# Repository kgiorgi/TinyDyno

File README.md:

# TinyDyno

An ESP32-S3 board that measures the speed and energy efficiency of one neural network inference.

**What is it exactly?**
TinyDyno is a custom 72 by 72 mm, 2 layered PCB based on ESP32-S3.It is basically a test bench for machine learning on tiny devices (AKA edgeAI). It runs a neural network based on the data from sensors and measures every inference for time and energy. Time is how long the inference took and energy is how much ESP32-S3 has used during it.

To account for actual use cases it has an IMU(motion sensor) and a microphone which are for gesture recognition and keyword detector so the usual run look something like this:
1. Record the input from either sensors
2. Run the same model on the same input but with different libraries.(My kernels VS Espressif's ESP-DL VS TensorFlow Lite Micro)
3. Measure each run using the INA226 (power monitor) which reports current/voltage going into the ESP32-S3 which does the power over time math
4. Get the results and make conclusions

(A test pad (TP1) goes high during each inference, so the timing can be checked independently with an oscilloscope or logic analyzer.)

**The WHY behind it all**

Wanting to optimize the field I am currently curious about (AI) I brainstormed for a bit and came to the conclusion that you can't optimize something that you can't measure. After a bit of digging I found few issues it would solve on top of the qol it would provide for me:
1. Most benchmarks only report speed so a faster kernel that uses more power can still drain the battery sooner.
2. The USB power meters are quite slow. They update a few times per second, while one inference takes about 5–50 ms.

(Also it's not like you can find stuff like this easily to buy)

**how does it work?**

**Power: two separate 3.3V rails**

USB-C gives 5V and two separate 3.3V regulators split it into two rails:
1. **Measured rail (3V3_MEAS):** 5V goes through regulator U2, then solder jumper JP1, then the 75 mOhm shunt resistor R3 and then into the ESP32-S3. The ESP32 is the only thing on this rail.
2. **Peripheral rail (3V3_PERIPH):** 5V goes through regulator U1 to everything else (INA226, IMU, mic, LED, pull-ups).

So none of the sensor or LED current goes through the shunt and the measurement is only the ESP32.

**Measuring power**

Current going through the shunt makes a small voltage across it (V = I * R). For example at 100mA it's 0.1A * 0.075 Ohm = 7.5mV, which is tiny, so the INA226 (U3) does the job:
1. measures the voltage across the shunt to get the current
2. measures the 3.3V rail to get the voltage
3. multiplies them to get power
4. pulls its ALERT pin low when a new reading is ready so the ESP32 knows when to read it

The shunt is read through a separate pair of thin traces that go straight from the shunt's pads to the INA226 (Kelvin sensing), so the voltage drop on the thick power traces doesn't mess up the reading.

**From power to energy and time**

Energy = power * time, so during an inference the ESP32 reads the power about once a millisecond and keeps adding up power * time. Time comes from the ESP32's internal microsecond timer.

One measurement looks like this:
1. Load the recorded input
2. Set TP1 high, start the timer and the energy sum
3. Run the model
4. Set TP1 low, stop, and send time and energy to the PC over USB

**Known problem**

The ESP32 reads its own power monitor, so the reading itself costs a bit of energy too. The plan is to do the measuring on one core and the model on the other, and subtract the idle power.

**Schematic and PCB**

1. Schematic: [hardware/kicad/TinyDyno.kicad_sch](hardware/kicad/TinyDyno.kicad_sch)
2. PCB: [hardware/kicad/TinyDyno.kicad_pcb](hardware/kicad/TinyDyno.kicad_pcb)
3. Gerbers, assembly BOM and placement file: [hardware/kicad/production/](hardware/kicad/production/)

**PCB design notes**

1. 2 layers, 72 by 72mm, 1.6mm thick, made in KiCad
2. GND pour on both layers with stitching vias
3. No copper under the ESP32 antenna
4. Track widths: 0.5mm for power, 0.25mm default, 0.2mm on fine-pitch pins
5. Vias are 0.6mm with 0.3mm holes. The ESP32 module's thermal vias were 0.2mm, so I enlarged them to 0.3mm to fit JLCPCB's 2-layer minimum
6. JP1 is a solder jumper that's closed by default. Cutting it opens the measured rail, so I can put a multimeter or bench supply in there to calibrate the INA226

**Pin map**

| Signal | ESP32-S3 pin |
|---|---|
| I2C SDA / SCL (INA226 and IMU) | IO4 / IO5 |
| INA226 ALERT (new reading ready) | IO6 |
| IMU interrupt (INT1) | IO7 |
| Mic DATA / CLK | IO41 / IO42 |
| Timing marker (TP1) | IO1 |
| Status LED (on when the pin is low) | IO2 |
| Boot button | IO0 |
| USB D- / D+ | IO19 / IO20 |

I2C addresses: INA226 is 0x40, IMU is 0x6A.

**What it can measure (INA226 + 75 mOhm shunt)**

| Item | Value |
|---|---|
| Current range | +/- 1.09A |
| Current resolution | about 33uA |
| Voltage resolution | 1.25mV |
| Fastest conversion | 140us (averaging adjustable) |
| Voltage lost across the shunt | about 37.5mV at 0.5A |

**BOM (bill of materials)**

Every part on the board. Everything is from LCSC and soldered by JLCPCB. Quantities are per board (2 boards get assembled).

Chips and main parts:

| Ref | Qty | Part | What it does | Package | LCSC |
|---|---|---|---|---|---|
| U4 | 1 | ESP32-S3-WROOM-1-N16R8 | Main microcontroller (16MB flash, 8MB PSRAM). Runs the models and the measuring | Module | [C2913202](https://www.lcsc.com/product-detail/C2913202.html) |
| U3 | 1 | INA226AIDGSR | Power monitor, measures current through R3 and the rail voltage | TSSOP-10 | [C49851](https://www.lcsc.com/product-detail/C49851.html) |
| U5 | 1 | LSM6DS3TR-C | 6-axis IMU (accelerometer + gyro), input for gesture models | LGA-14 | [C967633](https://www.lcsc.com/product-detail/C967633.html) |
| MK1 | 1 | IM69D130V01 | Digital PDM microphone, input for keyword detection | LLGA-5 | [C536262](https://www.lcsc.com/product-detail/C536262.html) |
| U1, U2 | 2 | LR1107G-33 | 3.3V regulators. U1 is for the peripheral rail, U2 for the measured rail | SOT-223 | [C171499](https://www.lcsc.com/product-detail/C171499.html) |
| R3 | 1 | 75 mOhm, 1%, 2512 | Shunt resistor in the ESP32's supply | 2512 | [C76252](https://www.lcsc.com/product-detail/C76252.html) |
| J1 | 1 | TYPE-C-31-M-12 | USB-C connector, 5V and USB data | SMD | [C165948](https://www.lcsc.com/product-detail/C165948.html) |
| SW1, SW2 | 2 | TS-1187A-B-A-B | Buttons. SW1 = reset (EN), SW2 = boot (IO0) | SMD | [C318884](https://www.lcsc.com/product-detail/C318884.html) |
| D1 | 1 | KT-0603R red LED | Status LED | 0603 | [C2286](https://www.lcsc.com/product-detail/C2286.html) |

Resistors:

| Ref | Qty | Value | What it does | Package | LCSC |
|---|---|---|---|---|---|
| R1, R2 | 2 | 5.1k | USB-C CC pull-downs, tell the PC/charger to give 5V | 0603 | [C23186](https://www.lcsc.com/product-detail/C23186.html) |
| R4, R5 | 2 | 5.1k | I2C pull-ups on SCL and SDA | 0603 | [C23186](https://www.lcsc.com/product-detail/C23186.html) |
| R6 | 1 | 5.1k | Pull-up for the INA226 ALERT line | 0603 | [C23186](https://www.lcsc.com/product-detail/C23186.html) |
| R7 | 1 | 10k | ESP32 EN (enable) pull-up | 0603 | [C25804](https://www.lcsc.com/product-detail/C25804.html) |
| R8 | 1 | 10k | IO0 (boot pin) pull-up so it boots normally | 0603 | [C25804](https://www.lcsc.com/product-detail/C25804.html) |
| R9, R11 | 2 | 22 Ohm | Series resistors on USB D+ / D- | 0603 | [C23345](https://www.lcsc.com/product-detail/C23345.html) |
| R10 | 1 | 1k | Current limit for the LED | 0603 | [C21190](https://www.lcsc.com/product-detail/C21190.html) |

Capacitors:

| Ref | Qty | Value | What it does | Package | LCSC |
|---|---|---|---|---|---|
| C1, C3 | 2 | 1uF | Input caps of the two regulators (5V side) | 0603 | [C15849](https://www.lcsc.com/product-detail/C15849.html) |
| C8 | 1 | 1uF | Together with R7 delays EN so the ESP32 starts cleanly | 0603 | [C15849](https://www.lcsc.com/product-detail/C15849.html) |
| C2 | 1 | 22uF | Output cap of U1 (peripheral rail) | 0805 | [C45783](https://www.lcsc.com/product-detail/C45783.html) |
| C4 | 1 | 22uF | Output cap of U2 (before the shunt) | 0805 | [C45783](https://www.lcsc.com/product-detail/C45783.html) |
| C6 | 1 | 22uF | Bulk cap at the ESP32 (after the shunt), handles Wi-Fi current spikes | 0805 | [C45783](https://www.lcsc.com/product-detail/C45783.html) |
| C7 | 1 | 100nF | Decoupling at the ESP32 power pin | 0603 | [C14663](https://www.lcsc.com/product-detail/C14663.html) |
| C5, C9, C10, C11 | 4 | 100nF | Decoupling for the INA226, IMU and mic | 0603 | [C14663](https://www.lcsc.com/product-detail/C14663.html) |

Not actual parts (just copper on the PCB):

| Ref | What it is |
|---|---|
| TP1 | Test pad, timing marker (high during an inference) |
| TP2 | Test pad, GND for the probe clip |
| JP1 | Solder jumper in the measured rail (closed by default) |

In total that's 32 parts per board, 16 different ones. The full exported list is in [hardware/kicad/production/bom.csv](hardware/kicad/production/bom.csv), and the cost list synced from Half Life is in [BOM.csv](BOM.csv).

**Cost (JLCPCB: 5 PCBs, 2 of them assembled)**

| Item | Cost |
|---|---|
| PCB, 2-layer, 72 by 72mm (x5) | $4.00 |
| ESP32-S3-WROOM-1-N16R8 (x2) | $10.29 |
| IM69D130V01 microphone (x2) | $6.25 |
| LSM6DS3TR-C IMU (x2) | $3.04 |
| INA226AIDGSR (x2) | $1.52 |
| LR1107G-33 regulators | $0.86 |
| 75 mOhm shunt resistors | $0.58 |
| USB-C connectors (x2) | $0.37 |
| Resistors, capacitors, LED and buttons | $2.42 |
| Standard assembly for 2 boards (setup, stencil, part loading, placement) | $66.86 |
| Shipping situational in my case 29.82 but I cover it | covered |
| **Total** | **96.19** |

**Fabrication notes**

1. Ordered from JLCPCB with Standard assembly, top side only. JLC adds 5mm edge rails on two sides, which you snap off along the V-cut.
2. U3 change: I planned to use the INA228 but it was out of stock at JLC, so I swapped it for the INA226. Same footprint and pin order, so the layout didn't change. The INA226 doesn't have a built-in energy counter, so the energy gets added up in firmware instead.
3. MK1 rotation: positions.csv says 180 degrees, but I rotated the mic by hand in JLC's placement preview. If you re-order, check it again.

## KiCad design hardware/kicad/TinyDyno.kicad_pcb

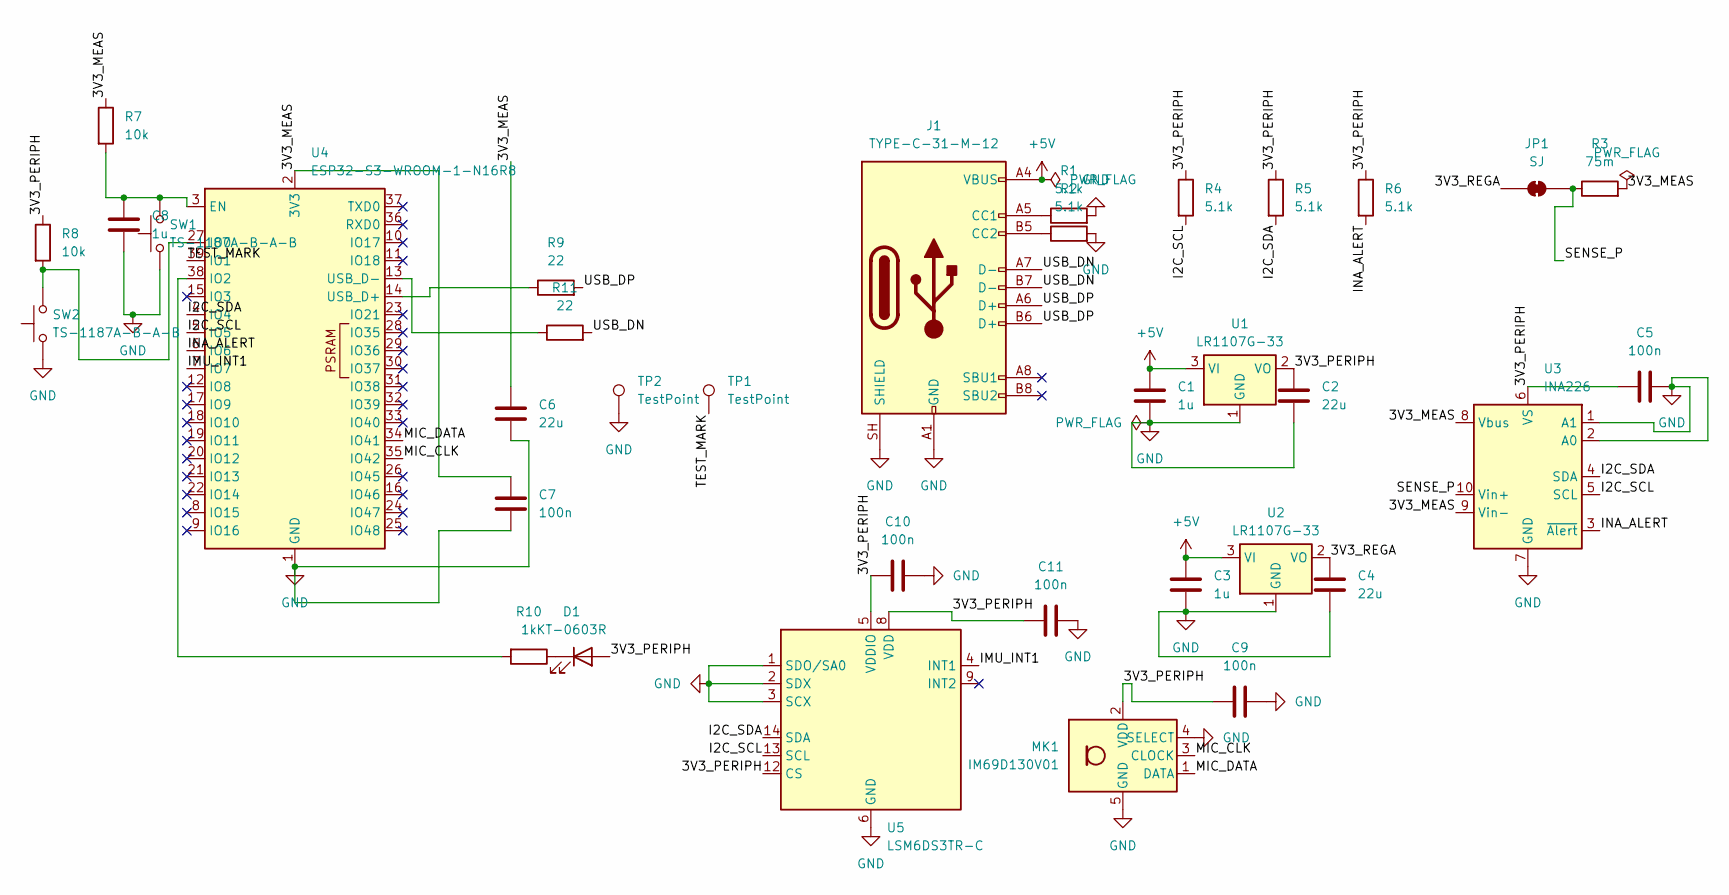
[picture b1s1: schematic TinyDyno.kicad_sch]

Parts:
C1, C3, C8: 1u; C_0603_1608Metric; LCSC C15849
C2, C4, C6: 22u; C_0805_2012Metric; LCSC C45783
C5, C7, C9, C10, C11: 100n; C_0603_1608Metric; LCSC C14663
D1: KT-0603R; LED_0603_1608Metric; LCSC C2286
J1: TYPE-C-31-M-12; USB_C_Receptacle_HRO_TYPE-C-31-M-12; LCSC C165948
JP1: SJ; SolderJumper-2_P1.3mm_Bridged_RoundedPad1.0x1.5mm
MK1: IM69D130V01; Infineon_PG-LLGA-5-1; LCSC C536262
R1, R2, R4, R5, R6: 5.1k; R_0603_1608Metric; LCSC C23186
R3: 75m; R_2512_6332Metric; LCSC C76252
R7, R8: 10k; R_0603_1608Metric; LCSC C25804
R9, R11: 22; R_0603_1608Metric; LCSC C23345
R10: 1k; R_0603_1608Metric; LCSC C21190
SW1, SW2: TS-1187A-B-A-B; SW_Push_1P1T_XKB_TS-1187A; LCSC C318884
TP1, TP2: TestPoint; TestPoint_Pad_D1.5mm
U1, U2: LR1107G-33; SOT-223-3_TabPin2; LCSC C171499
U3: INA226; TSSOP-10_3x3mm_P0.5mm; LCSC C49851
U4: ESP32-S3-WROOM-1-N16R8; ESP32-S3-WROOM-1; LCSC C2913202
U5: LSM6DS3TR-C; LGA-14_3x2.5mm_P0.5mm_LayoutBorder3x4y; LCSC C967633

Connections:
+5V: C1.1, C3.1, J1.A4 (VBUS), J1.A9 (VBUS), J1.B4 (VBUS), J1.B9 (VBUS), U1.3 (VI), U2.3 (VI)
/3V3_MEAS: C6.1, C7.1, R3.2, R7.1, U3.8 (Vbus), U3.9 (Vin-), U4.2 (3V3)
/3V3_PERIPH: C2.1, C5.1, C9.1, C10.1, C11.1, D1.2 (A), MK1.2 (VDD), R4.1, R5.1, R6.1, R8.1, U1.2 (VO), U3.6 (VS), U5.5 (VDDIO), U5.8 (VDD), U5.12 (CS)
/3V3_REGA: C4.1, JP1.1 (A), U2.2 (VO)
/I2C_SCL: R4.2, U3.5 (SCL), U4.5 (IO5), U5.13 (SCL)
/I2C_SDA: R5.2, U3.4 (SDA), U4.4 (IO4), U5.14 (SDA)
/IMU_INT1: U4.7 (IO7), U5.4 (INT1)
/INA_ALERT: R6.2, U3.3 (~Alert), U4.6 (IO6)
/MIC_CLK: MK1.3 (CLOCK), U4.35 (IO42)
/MIC_DATA: MK1.1 (DATA), U4.34 (IO41)
/SENSE_P: JP1.2 (B), R3.1, U3.10 (Vin+)
/TEST_MARK: TP1.1 (1_1), U4.39 (IO1)
/USB_DN: J1.A7 (D-), J1.B7 (D-), R11.2
/USB_DP: J1.A6 (D+), J1.B6 (D+), R9.2
GND: C1.2, C2.2, C3.2, C4.2, C5.2, C6.2, C7.2, C8.2, C9.2, C10.2, C11.2, J1.A1 (GND), J1.A12 (GND), J1.B1 (GND), J1.B12 (GND), J1.SH (SHIELD), MK1.4 (SELECT), MK1.5 (GND), R1.2, R2.2, SW1.1, SW2.1, TP2.1 (1_1), U1.1 (GND), U2.1 (GND), U3.1 (A1), U3.2 (A0), U3.7 (GND), U4.1 (GND), U4.40 (GND), U4.41 (GND), U5.1 (SDO/SA0), U5.2 (SDX), U5.3 (SCX), U5.6 (GND), U5.7 (GND)
unnamed: D1.1 (K), R10.1
unnamed: J1.A5 (CC1), R1.1
unnamed: J1.B5 (CC2), R2.1
unnamed: C8.1, R7.2, SW1.2, U4.3 (EN)
unnamed: R8.2, SW2.2, U4.27 (IO0)
unnamed: R10.2, U4.38 (IO2)
unnamed: R9.1, U4.14 (USB_D+)
unnamed: R11.1, U4.13 (USB_D-)

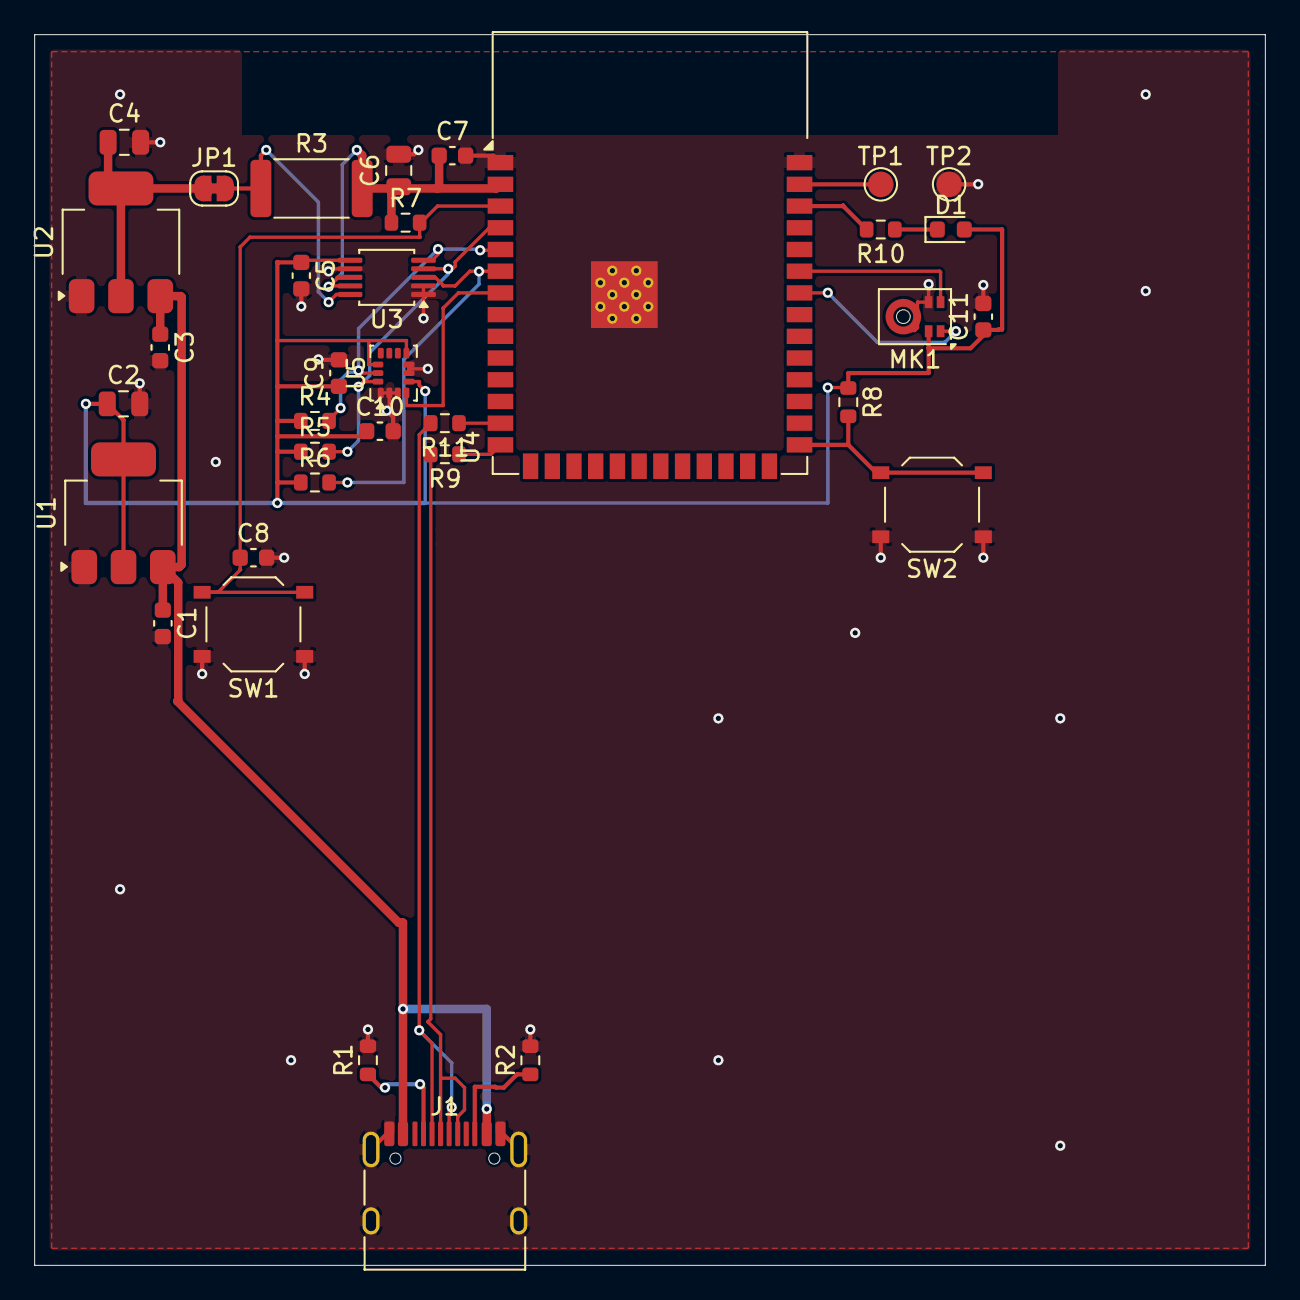
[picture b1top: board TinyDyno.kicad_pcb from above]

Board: 2 copper layers, 72.0 x 72.0 mm, 35 parts (0 on the bottom side), 23 nets.

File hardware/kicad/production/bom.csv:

Designator,Footprint,Quantity,Value,LCSC Part #
"C1, C3, C8",0603,3,1u,C15849
"C10, C11, C5, C7, C9",0603,5,100n,C14663
"C2, C4, C6",0805,3,22u,C45783
D1,0603,1,KT-0603R,C2286
J1,USB_C_Receptacle_HRO_TYPE-C-31-M-12,1,TYPE-C-31-M-12,C165948
MK1,Infineon_PG-LLGA-5-1,1,IM69D130V01,C536262
"R1, R2, R4, R5, R6",0603,5,5.1k,C23186
R10,0603,1,1k,C21190
"R11, R9",0603,2,22,C23345
R3,2512,1,75m,C76252
"R7, R8",0603,2,10k,C25804
"SW1, SW2",SW_Push_1P1T_XKB_TS-1187A,2,TS-1187A-B-A-B,C318884
"U1, U2",SOT-223-3_TabPin2,2,LR1107G-33,C171499
U3,TSSOP-10_3x3mm_P0.5mm,1,INA226, C49851
U4,ESP32-S3-WROOM-1,1,ESP32-S3-WROOM-1-N16R8, C2913202
U5,LGA-14_3x2.5mm_P0.5mm_LayoutBorder3x4y,1,LSM6DS3TR-C,C967633

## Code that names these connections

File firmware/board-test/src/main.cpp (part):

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constexpr int PIN_MARK = 1;
constexpr int PIN_SDA = 4;
constexpr int PIN_SCL = 5;
constexpr int PIN_INA_ALERT = 6;
constexpr int PIN_IMU_INT1 = 7;
constexpr int PIN_MIC_CLK = 42;
constexpr int PIN_MIC_DATA = 41;
constexpr bool LED_ON = 0;
constexpr bool LED_OFF = 1;

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
void testInaAlert()
{
    pinMode(PIN_INA_ALERT, INPUT_PULLUP);
    uint16_t dummy;
    i2cWrite16(INA_ADDR, INA_MASK, INA_MASK_CNVR);
    i2cRead16(INA_ADDR, INA_MASK, dummy);
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    bool sawLow = false;
    uint32_t t0 = millis();
    while (millis() - t0 < 200 && !sawLow)
        sawLow = digitalRead(PIN_INA_ALERT) == 0;

    i2cRead16(INA_ADDR, INA_MASK, dummy);
    i2cWrite16(INA_ADDR, INA_MASK, 0x0000);
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
void testImuInt()
{
    pinMode(PIN_IMU_INT1, INPUT);
    readImu();
    i2cWrite8(IMU_ADDR, IMU_INT1_CTRL, 0x01);

    bool sawHigh = false;
    uint32_t t0 = millis();
    while (millis() - t0 < 100 && !sawHigh)
        sawHigh = digitalRead(PIN_IMU_INT1) == 1;

    i2cWrite8(IMU_ADDR, IMU_INT1_CTRL, 0x00);
    report("imu int1", sawHigh, sawHigh ? "IO7 went HIGH on data ready" : "IO7 never went HIGH");
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
void testMic()
{
    mic.setPinsPdmRx(PIN_MIC_CLK, PIN_MIC_DATA);
    if (!mic.begin(I2S_MODE_PDM_RX, MIC_RATE, I2S_DATA_BIT_WIDTH_16BIT, I2S_SLOT_MODE_STEREO))
    {
        report("mic", false, "I2S PDM driver failed to start");
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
